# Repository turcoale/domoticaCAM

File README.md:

# domoticaCAM

# Desarrollo de Hardware y Software de placa de efecto FADE-IN FADE-OUT para sistema de iluminación con microcontrolador
# FREESCALE

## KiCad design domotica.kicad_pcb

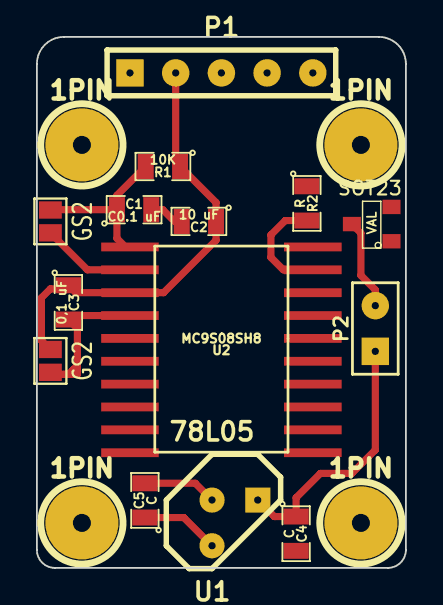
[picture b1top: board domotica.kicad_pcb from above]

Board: 2 copper layers, 20.5 x 29.5 mm, 18 parts (0 on the bottom side), 9 nets.

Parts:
1PIN, 1PIN#2, 1PIN#3, 1PIN#4: P***; 1pin
C1: C0.1 uF; SM0805
C2: 10 uF; SM0805
C3: 0,1 uF; SM0805
C4, C5: C; SM0805
GS2, GS2#2: VAL*; GS2
P1: CONN_5; PIN_ARRAY_5x1
P2: CONN_2; PIN_ARRAY_2X1
R1: 10K; SM0805
R2: R; SM0805
SOT23: VAL; SOT23
U1: 78L05; TO92
U2: MC9S08SH8; SOIC-20

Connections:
+12V: C4.1, P2.1, U1.1
/BDM: GS2.2, U2.2
/OUT: P1.4, U2.12
/RESET: C1.1, GS2.1, R1.2, U2.1
/VDD: C2.1, C3.1, C5.1, GS2#2.1, P1.2, R1.1, U1.3, U2.3
GND: C1.2, C2.2, C3.2, C4.2, C5.2, GS2#2.2, P1.5, SOT23.2, U1.2, U2.4
unnamed: P2.2, SOT23.3
unnamed: R2.1, SOT23.1
unnamed: R2.2, U2.19

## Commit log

2015-04-07 agrego firmware
2015-04-07 algunos pdf
